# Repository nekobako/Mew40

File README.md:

| English | [日本語](README-ja-jp.md) |

# Mew40
A low-profile, unibody keyboard with a 40% ortholinear layout.

## Key Features
- 48-key ortholinear layout arranged in 4 rows of 12 keys
- Hot-swappable 3-pin switches compatible with Choc V2
- Full color backlighting for every key
- Choice of an aluminum case machined by CNC or a resin case made with 3D printing
- Keymap customization with Vial

## Build Guide
[Build Guide | Mew40](https://mew40.nekobako.net/build-guide/)

## License
| Component | License | Third Party Notices |
| --- | --- | --- |
| [PCB](./PCB/) | [LICENSE.md](./PCB/LICENSE.md) | [THIRD-PARTY-NOTICES.md](./PCB/THIRD-PARTY-NOTICES.md) |
| [Case](./Case/) | [LICENSE.md](./Case/LICENSE.md) | [THIRD-PARTY-NOTICES.md](./Case/THIRD-PARTY-NOTICES.md) |
| [Firmware](./Firmware/) | [LICENSE.md](./Firmware/LICENSE.md) | [THIRD-PARTY-NOTICES.md](./Firmware/THIRD-PARTY-NOTICES.md) |

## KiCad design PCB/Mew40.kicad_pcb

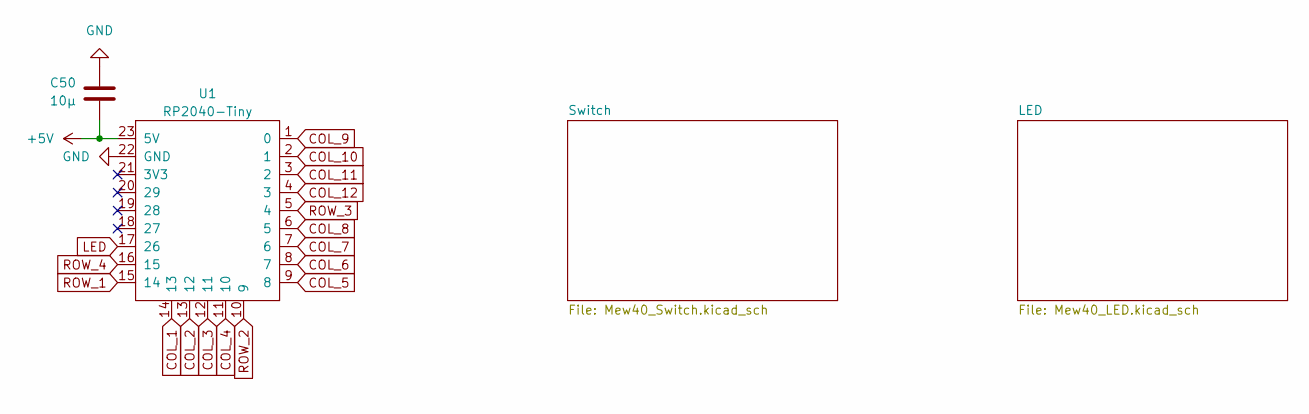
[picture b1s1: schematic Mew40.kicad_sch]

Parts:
C50: 10µ; C_1206_3216Metric
U1: RP2040-Tiny; Waveshare_RP2040-Zero_SMD

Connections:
+5V: C50.2, U1.23 (5V); also elsewhere on the board
COL_1: U1.14 (13); also elsewhere on the board
COL_2: U1.13 (12); also elsewhere on the board
COL_3: U1.12 (11); also elsewhere on the board
COL_4: U1.11 (10); also elsewhere on the board
COL_5: U1.9 (8); also elsewhere on the board
COL_6: U1.8 (7); also elsewhere on the board
COL_7: U1.7 (6); also elsewhere on the board
COL_8: U1.6 (5); also elsewhere on the board
COL_9: U1.1 (0); also elsewhere on the board
COL_10: U1.2 (1); also elsewhere on the board
COL_11: U1.3 (2); also elsewhere on the board
COL_12: U1.4 (3); also elsewhere on the board
GND: C50.1, U1.22 (GND); also elsewhere on the board
LED: U1.17 (26); also elsewhere on the board
ROW_1: U1.15 (14); also elsewhere on the board
ROW_2: U1.10 (9); also elsewhere on the board
ROW_3: U1.5 (4); also elsewhere on the board
ROW_4: U1.16 (15); also elsewhere on the board

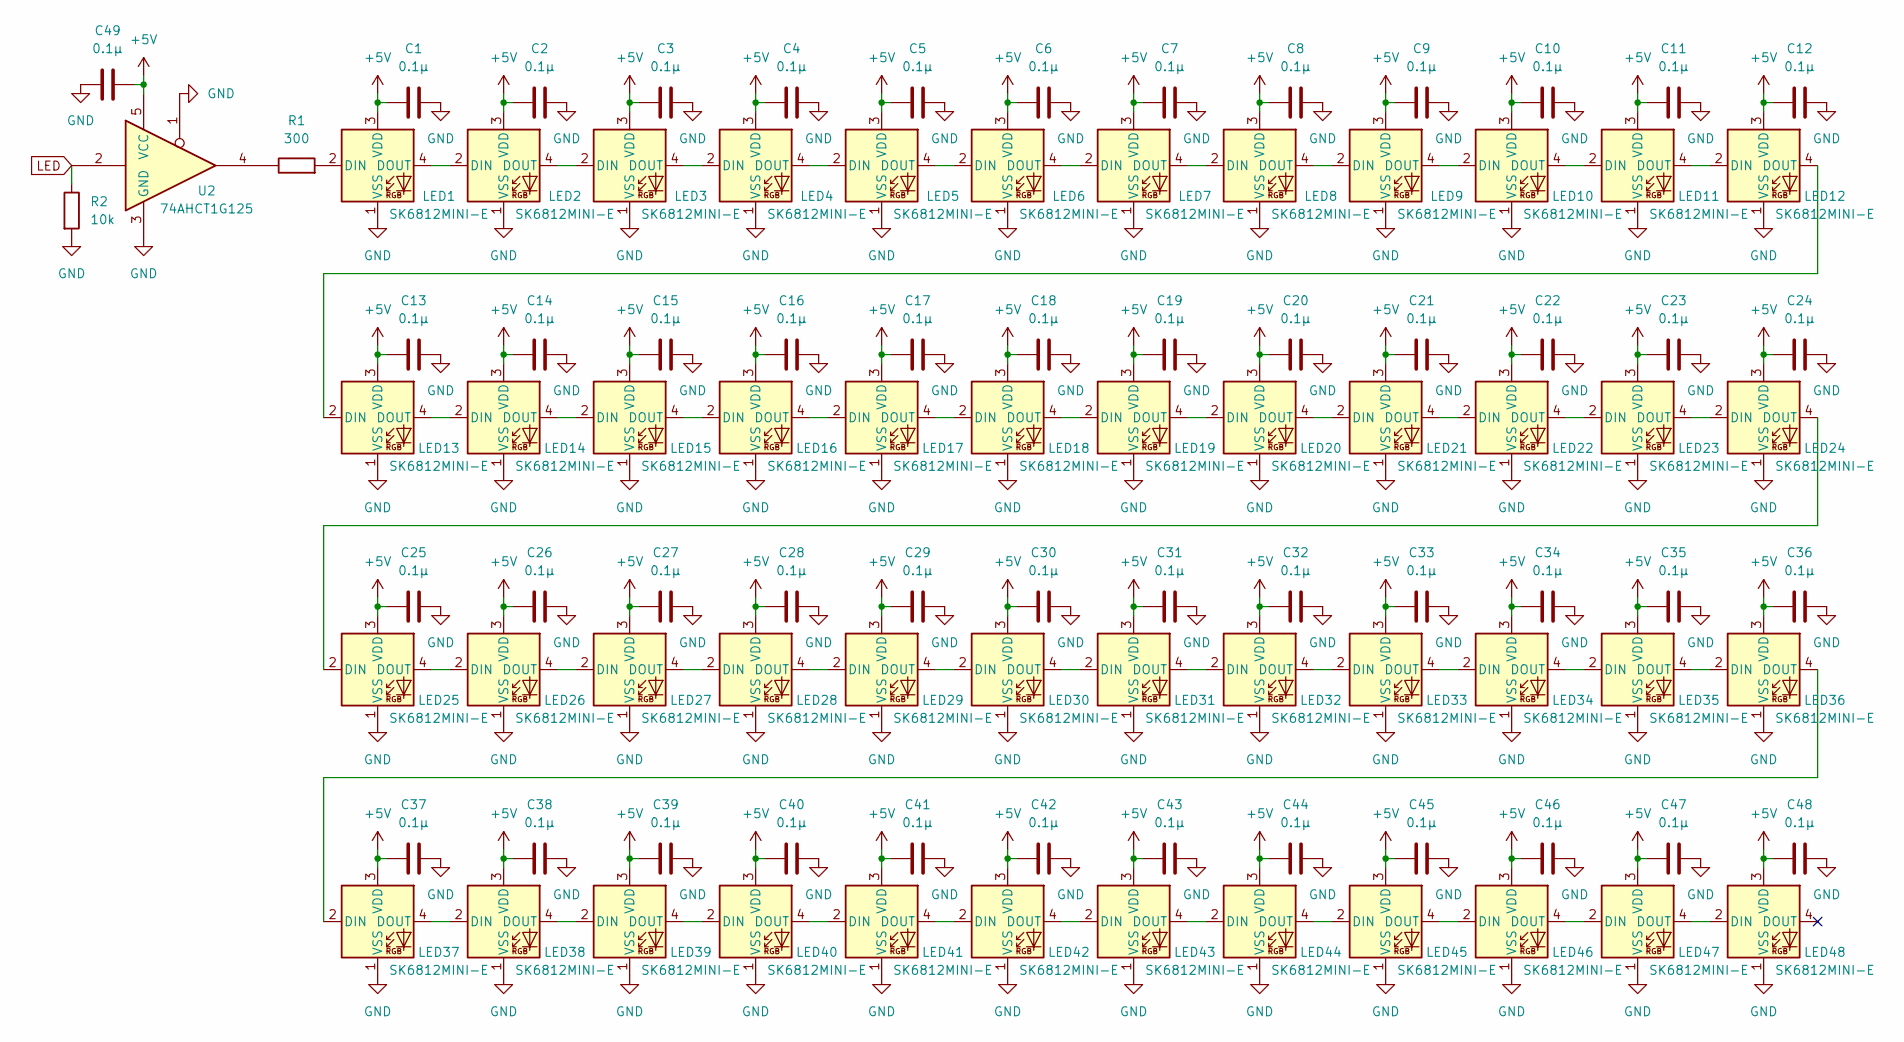
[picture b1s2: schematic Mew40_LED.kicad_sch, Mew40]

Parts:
C1, C2, C3, C4, C5, C6, C7, C8, C9, C10, C11, C12, C13, C14, C15, C16, C17, C18, C19, C20, C21, C22, C23, C24, C25, C26, C27, C28, C29, C30, C31, C32, C33, C34, C35, C36, C37, C38, C39, C40, C41, C42, C43, C44, C45, C46, C47, C48, C49: 0.1µ; C_0603_1608Metric
LED1, LED2, LED3, LED4, LED5, LED6, LED7, LED8, LED9, LED10, LED11, LED12, LED13, LED14, LED15, LED16, LED17, LED18, LED19, LED20, LED21, LED22, LED23, LED24, LED25, LED26, LED27, LED28, LED29, LED30, LED31, LED32, LED33, LED34, LED35, LED36, LED37, LED38, LED39, LED40, LED41, LED42, LED43, LED44, LED45, LED46, LED47, LED48: SK6812MINI-E; LED_SK6812MINI-E_3.2x2.8mm_P1.5mm_ReverseMount
R1: 300; R_0603_1608Metric
R2: 10k; R_0603_1608Metric
U2: 74AHCT1G125; SOT-23-5

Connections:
+5V: C1.1, C2.1, C3.1, C4.1, C5.1, C6.1, C7.1, C8.1, C9.1, C10.1, C11.1, C12.1, C13.1, C14.1, C15.1, C16.1, C17.1, C18.1, C19.1, C20.1, C21.1, C22.1, C23.1, C24.1, C25.1, C26.1, C27.1, C28.1, C29.1, C30.1, C31.1, C32.1, C33.1, C34.1, C35.1, C36.1, C37.1, C38.1, C39.1, C40.1, C41.1, C42.1, C43.1, C44.1, C45.1, C46.1, C47.1, C48.1, C49.2, LED1.3 (VDD), LED2.3 (VDD), LED3.3 (VDD), LED4.3 (VDD), LED5.3 (VDD), LED6.3 (VDD), LED7.3 (VDD), LED8.3 (VDD), LED9.3 (VDD), LED10.3 (VDD), LED11.3 (VDD), LED12.3 (VDD), LED13.3 (VDD), LED14.3 (VDD), LED15.3 (VDD), LED16.3 (VDD), LED17.3 (VDD), LED18.3 (VDD), LED19.3 (VDD), LED20.3 (VDD), LED21.3 (VDD), LED22.3 (VDD), LED23.3 (VDD), LED24.3 (VDD), LED25.3 (VDD), LED26.3 (VDD), LED27.3 (VDD), LED28.3 (VDD), LED29.3 (VDD), LED30.3 (VDD), LED31.3 (VDD), LED32.3 (VDD), LED33.3 (VDD), LED34.3 (VDD), LED35.3 (VDD), LED36.3 (VDD), LED37.3 (VDD), LED38.3 (VDD), LED39.3 (VDD), LED40.3 (VDD), LED41.3 (VDD), LED42.3 (VDD), LED43.3 (VDD), LED44.3 (VDD), LED45.3 (VDD), LED46.3 (VDD), LED47.3 (VDD), LED48.3 (VDD), U2.5 (VCC); also elsewhere on the board
GND: C1.2, C2.2, C3.2, C4.2, C5.2, C6.2, C7.2, C8.2, C9.2, C10.2, C11.2, C12.2, C13.2, C14.2, C15.2, C16.2, C17.2, C18.2, C19.2, C20.2, C21.2, C22.2, C23.2, C24.2, C25.2, C26.2, C27.2, C28.2, C29.2, C30.2, C31.2, C32.2, C33.2, C34.2, C35.2, C36.2, C37.2, C38.2, C39.2, C40.2, C41.2, C42.2, C43.2, C44.2, C45.2, C46.2, C47.2, C48.2, C49.1, LED1.1 (VSS), LED2.1 (VSS), LED3.1 (VSS), LED4.1 (VSS), LED5.1 (VSS), LED6.1 (VSS), LED7.1 (VSS), LED8.1 (VSS), LED9.1 (VSS), LED10.1 (VSS), LED11.1 (VSS), LED12.1 (VSS), LED13.1 (VSS), LED14.1 (VSS), LED15.1 (VSS), LED16.1 (VSS), LED17.1 (VSS), LED18.1 (VSS), LED19.1 (VSS), LED20.1 (VSS), LED21.1 (VSS), LED22.1 (VSS), LED23.1 (VSS), LED24.1 (VSS), LED25.1 (VSS), LED26.1 (VSS), LED27.1 (VSS), LED28.1 (VSS), LED29.1 (VSS), LED30.1 (VSS), LED31.1 (VSS), LED32.1 (VSS), LED33.1 (VSS), LED34.1 (VSS), LED35.1 (VSS), LED36.1 (VSS), LED37.1 (VSS), LED38.1 (VSS), LED39.1 (VSS), LED40.1 (VSS), LED41.1 (VSS), LED42.1 (VSS), LED43.1 (VSS), LED44.1 (VSS), LED45.1 (VSS), LED46.1 (VSS), LED47.1 (VSS), LED48.1 (VSS), R2.2, U2.1, U2.3 (GND); also elsewhere on the board
LED: R2.1, U2.2; also elsewhere on the board
unnamed: LED1.2 (DIN), R1.2
unnamed: LED1.4 (DOUT), LED2.2 (DIN)
unnamed: LED2.4 (DOUT), LED3.2 (DIN)
unnamed: LED3.4 (DOUT), LED4.2 (DIN)
unnamed: LED4.4 (DOUT), LED5.2 (DIN)
unnamed: LED5.4 (DOUT), LED6.2 (DIN)
unnamed: LED6.4 (DOUT), LED7.2 (DIN)
unnamed: LED7.4 (DOUT), LED8.2 (DIN)
unnamed: LED8.4 (DOUT), LED9.2 (DIN)
unnamed: LED9.4 (DOUT), LED10.2 (DIN)
unnamed: LED10.4 (DOUT), LED11.2 (DIN)
unnamed: LED11.4 (DOUT), LED12.2 (DIN)
unnamed: LED12.4 (DOUT), LED13.2 (DIN)
unnamed: LED13.4 (DOUT), LED14.2 (DIN)
unnamed: LED14.4 (DOUT), LED15.2 (DIN)
unnamed: LED15.4 (DOUT), LED16.2 (DIN)
unnamed: LED16.4 (DOUT), LED17.2 (DIN)
unnamed: LED17.4 (DOUT), LED18.2 (DIN)
unnamed: LED18.4 (DOUT), LED19.2 (DIN)
unnamed: LED19.4 (DOUT), LED20.2 (DIN)
unnamed: LED20.4 (DOUT), LED21.2 (DIN)
unnamed: LED21.4 (DOUT), LED22.2 (DIN)
unnamed: LED22.4 (DOUT), LED23.2 (DIN)
unnamed: LED23.4 (DOUT), LED24.2 (DIN)
unnamed: LED24.4 (DOUT), LED25.2 (DIN)
unnamed: LED25.4 (DOUT), LED26.2 (DIN)
unnamed: LED26.4 (DOUT), LED27.2 (DIN)
unnamed: LED27.4 (DOUT), LED28.2 (DIN)
unnamed: LED28.4 (DOUT), LED29.2 (DIN)
unnamed: LED29.4 (DOUT), LED30.2 (DIN)
unnamed: LED30.4 (DOUT), LED31.2 (DIN)
unnamed: LED31.4 (DOUT), LED32.2 (DIN)
unnamed: LED32.4 (DOUT), LED33.2 (DIN)
unnamed: LED33.4 (DOUT), LED34.2 (DIN)
unnamed: LED34.4 (DOUT), LED35.2 (DIN)
unnamed: LED35.4 (DOUT), LED36.2 (DIN)
unnamed: LED36.4 (DOUT), LED37.2 (DIN)
unnamed: LED37.4 (DOUT), LED38.2 (DIN)
unnamed: LED38.4 (DOUT), LED39.2 (DIN)
unnamed: LED39.4 (DOUT), LED40.2 (DIN)
unnamed: LED40.4 (DOUT), LED41.2 (DIN)
unnamed: LED41.4 (DOUT), LED42.2 (DIN)
unnamed: LED42.4 (DOUT), LED43.2 (DIN)
unnamed: LED43.4 (DOUT), LED44.2 (DIN)
unnamed: LED44.4 (DOUT), LED45.2 (DIN)
unnamed: LED45.4 (DOUT), LED46.2 (DIN)
unnamed: LED46.4 (DOUT), LED47.2 (DIN)
unnamed: LED47.4 (DOUT), LED48.2 (DIN)
unnamed: R1.1, U2.4

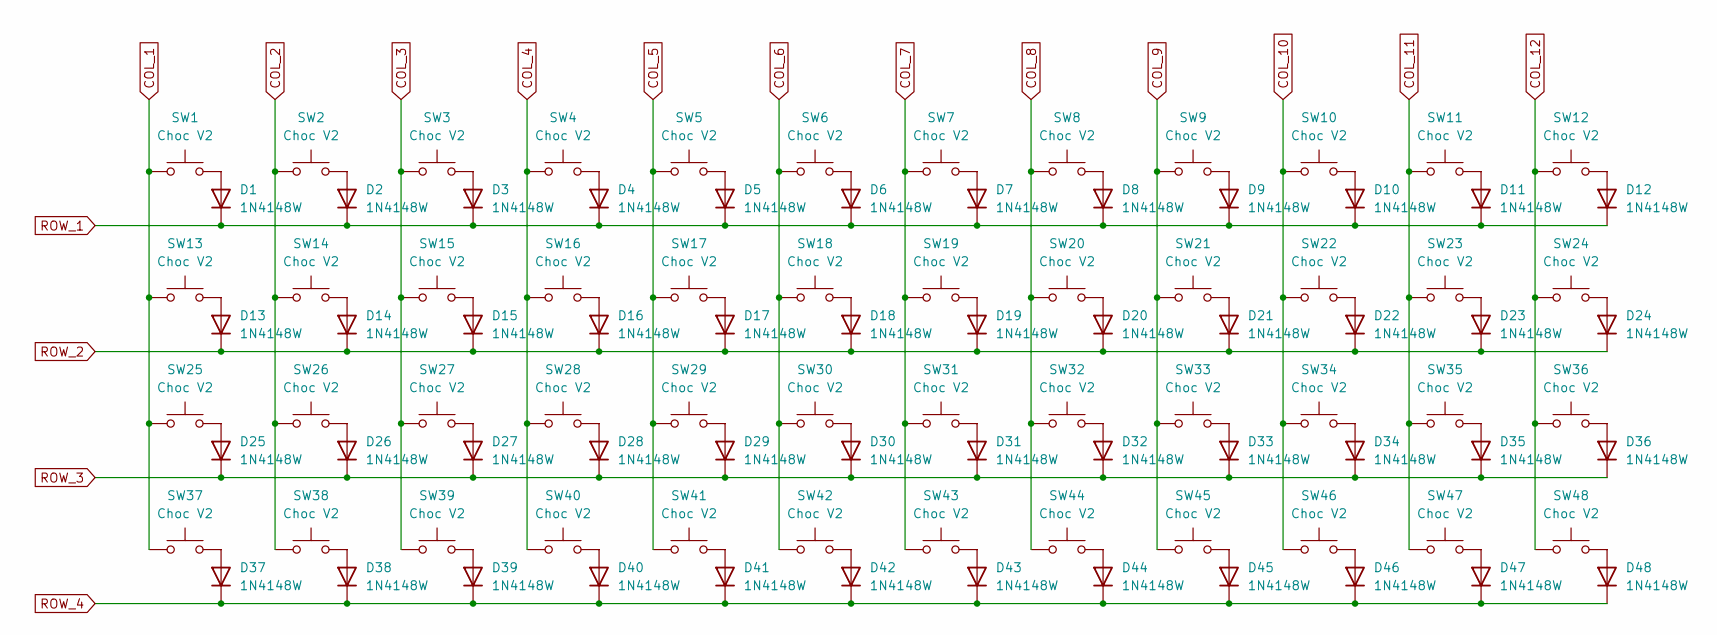
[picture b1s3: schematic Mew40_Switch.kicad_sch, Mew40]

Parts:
D1, D2, D3, D4, D5, D6, D7, D8, D9, D10, D11, D12, D13, D14, D15, D16, D17, D18, D19, D20, D21, D22, D23, D24, D25, D26, D27, D28, D29, D30, D31, D32, D33, D34, D35, D36, D37, D38, D39, D40, D41, D42, D43, D44, D45, D46, D47, D48: 1N4148W; D_SOD-123
SW1, SW2, SW3, SW4, SW5, SW6, SW7, SW8, SW9, SW10, SW11, SW12, SW13, SW14, SW15, SW16, SW17, SW18, SW19, SW20, SW21, SW22, SW23, SW24, SW25, SW26, SW27, SW28, SW29, SW30, SW31, SW32, SW33, SW34, SW35, SW36, SW37, SW38, SW39, SW40, SW41, SW42, SW43, SW44, SW45, SW46, SW47, SW48: Choc V2; SW_choc_v2_1u

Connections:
COL_1: SW1.1, SW13.1, SW25.1, SW37.1; also elsewhere on the board
COL_2: SW2.1, SW14.1, SW26.1, SW38.1; also elsewhere on the board
COL_3: SW3.1, SW15.1, SW27.1, SW39.1; also elsewhere on the board
COL_4: SW4.1, SW16.1, SW28.1, SW40.1; also elsewhere on the board
COL_5: SW5.1, SW17.1, SW29.1, SW41.1; also elsewhere on the board
COL_6: SW6.1, SW18.1, SW30.1, SW42.1; also elsewhere on the board
COL_7: SW7.1, SW19.1, SW31.1, SW43.1; also elsewhere on the board
COL_8: SW8.1, SW20.1, SW32.1, SW44.1; also elsewhere on the board
COL_9: SW9.1, SW21.1, SW33.1, SW45.1; also elsewhere on the board
COL_10: SW10.1, SW22.1, SW34.1, SW46.1; also elsewhere on the board
COL_11: SW11.1, SW23.1, SW35.1, SW47.1; also elsewhere on the board
COL_12: SW12.1, SW24.1, SW36.1, SW48.1; also elsewhere on the board
unnamed: D1.2 (A), SW1.2
unnamed: D2.2 (A), SW2.2
unnamed: D3.2 (A), SW3.2
unnamed: D4.2 (A), SW4.2
unnamed: D5.2 (A), SW5.2
unnamed: D6.2 (A), SW6.2
unnamed: D7.2 (A), SW7.2
unnamed: D8.2 (A), SW8.2
unnamed: D9.2 (A), SW9.2
unnamed: D10.2 (A), SW10.2
unnamed: D11.2 (A), SW11.2
unnamed: D12.2 (A), SW12.2
unnamed: D13.2 (A), SW13.2
unnamed: D14.2 (A), SW14.2
unnamed: D15.2 (A), SW15.2
unnamed: D16.2 (A), SW16.2
unnamed: D17.2 (A), SW17.2
unnamed: D18.2 (A), SW18.2
unnamed: D19.2 (A), SW19.2
unnamed: D20.2 (A), SW20.2
unnamed: D21.2 (A), SW21.2
unnamed: D22.2 (A), SW22.2
unnamed: D23.2 (A), SW23.2
unnamed: D24.2 (A), SW24.2
unnamed: D25.2 (A), SW25.2
unnamed: D26.2 (A), SW26.2
unnamed: D27.2 (A), SW27.2
unnamed: D28.2 (A), SW28.2
unnamed: D29.2 (A), SW29.2
unnamed: D30.2 (A), SW30.2
unnamed: D31.2 (A), SW31.2
unnamed: D32.2 (A), SW32.2
unnamed: D33.2 (A), SW33.2
unnamed: D34.2 (A), SW34.2
unnamed: D35.2 (A), SW35.2
unnamed: D36.2 (A), SW36.2
unnamed: D37.2 (A), SW37.2
unnamed: D38.2 (A), SW38.2
unnamed: D39.2 (A), SW39.2
unnamed: D40.2 (A), SW40.2
unnamed: D41.2 (A), SW41.2
unnamed: D42.2 (A), SW42.2
unnamed: D43.2 (A), SW43.2
unnamed: D44.2 (A), SW44.2
unnamed: D45.2 (A), SW45.2
unnamed: D46.2 (A), SW46.2
unnamed: D47.2 (A), SW47.2
unnamed: D48.2 (A), SW48.2
ROW_1: D1.1 (K), D2.1 (K), D3.1 (K), D4.1 (K), D5.1 (K), D6.1 (K), D7.1 (K), D8.1 (K), D9.1 (K), D10.1 (K), D11.1 (K), D12.1 (K); also elsewhere on the board
ROW_2: D13.1 (K), D14.1 (K), D15.1 (K), D16.1 (K), D17.1 (K), D18.1 (K), D19.1 (K), D20.1 (K), D21.1 (K), D22.1 (K), D23.1 (K), D24.1 (K); also elsewhere on the board
ROW_3: D25.1 (K), D26.1 (K), D27.1 (K), D28.1 (K), D29.1 (K), D30.1 (K), D31.1 (K), D32.1 (K), D33.1 (K), D34.1 (K), D35.1 (K), D36.1 (K); also elsewhere on the board
ROW_4: D37.1 (K), D38.1 (K), D39.1 (K), D40.1 (K), D41.1 (K), D42.1 (K), D43.1 (K), D44.1 (K), D45.1 (K), D46.1 (K), D47.1 (K), D48.1 (K); also elsewhere on the board

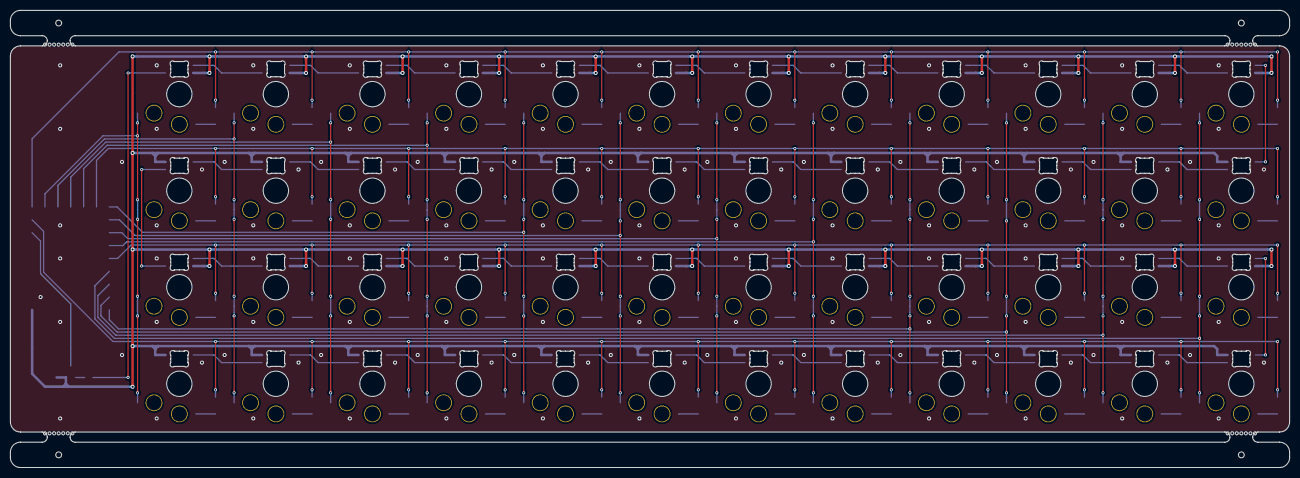
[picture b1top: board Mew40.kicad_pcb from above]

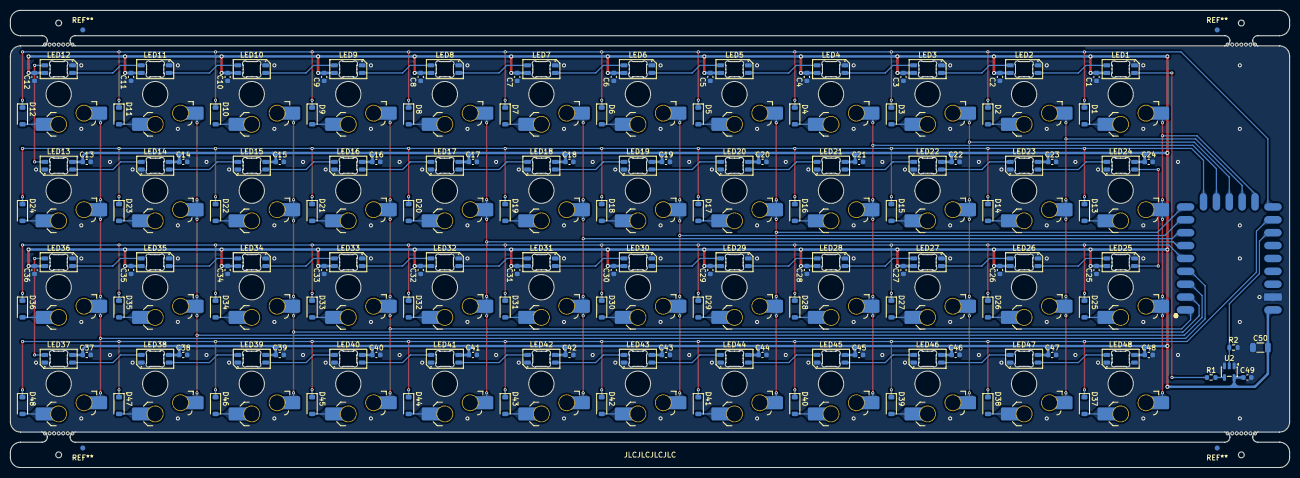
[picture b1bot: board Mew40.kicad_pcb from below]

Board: 2 copper layers, 252.4 x 90.2 mm, 198 parts (198 on the bottom side), 116 nets.
